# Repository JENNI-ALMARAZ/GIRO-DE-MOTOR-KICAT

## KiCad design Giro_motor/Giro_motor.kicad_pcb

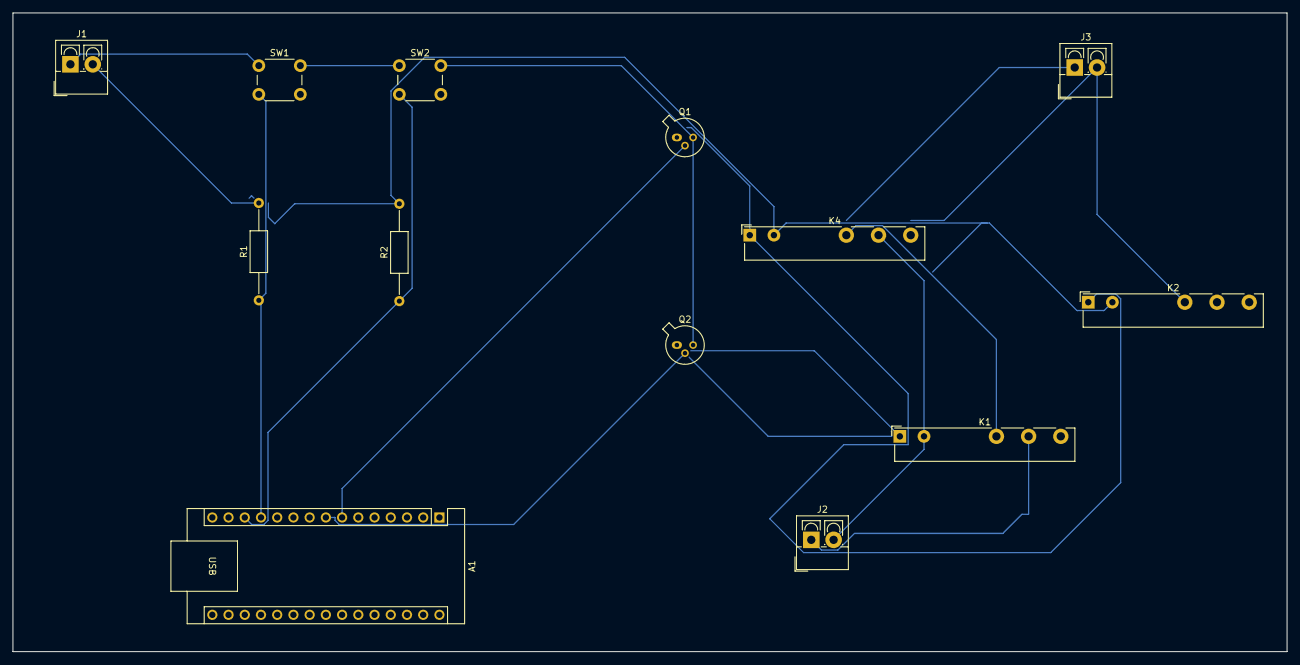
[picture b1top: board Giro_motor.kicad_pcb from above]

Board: 2 copper layers, 199.5 x 100.0 mm, 13 parts (0 on the bottom side), 11 nets.

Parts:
A1: Arduino_Nano_v2.x; Arduino_Nano
J1, J2, J3: Screw_Terminal_01x02; TerminalBlock_4Ucon_1x02_P3.50mm_Vertical
K1, K2, K4: Fujitsu_FTR-LYCA005x; Relay_SPDT_Fujitsu_FTR-LYCA005x_FormC_Vertical
Q1, Q2: BC107; TO-18-3
R1, R2: R; R_Axial_DIN0207_L6.3mm_D2.5mm_P15.24mm_Horizontal
SW1, SW2: SW_Push; SW_PUSH_6mm

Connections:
+5V: J1.1, Q1.3 (C), Q2.3 (C), SW1.1, SW2.1
GND: J1.2, J2.2, K1.A2, K2.A2, K4.11, K4.A2, R1.2, R2.2
unnamed: A1.7 (D4), Q1.2 (B)
unnamed: A1.8 (D5), Q2.2 (B)
unnamed: A1.12 (D9), R1.1, SW1.2
unnamed: A1.13 (D10), R2.1, SW2.2
unnamed: J2.1, K1.11
unnamed: J3.1, K1.12, K4.12
unnamed: J3.2, K2.12, K4.14
unnamed: K2.A1, K4.A1, Q1.1 (E)
unnamed: K1.A1, Q2.1 (E)
